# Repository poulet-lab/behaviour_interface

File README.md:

# Behavior Interface

Interface between a data acquisition device on one end as well as, both,
1) input from capacitive lick sensors, and
2) reward output to valves on the other end.

Digital events (licks, rewards) are displayed by means of LEDs.
Circuit breakers can be used to reset the capacitive sensors.

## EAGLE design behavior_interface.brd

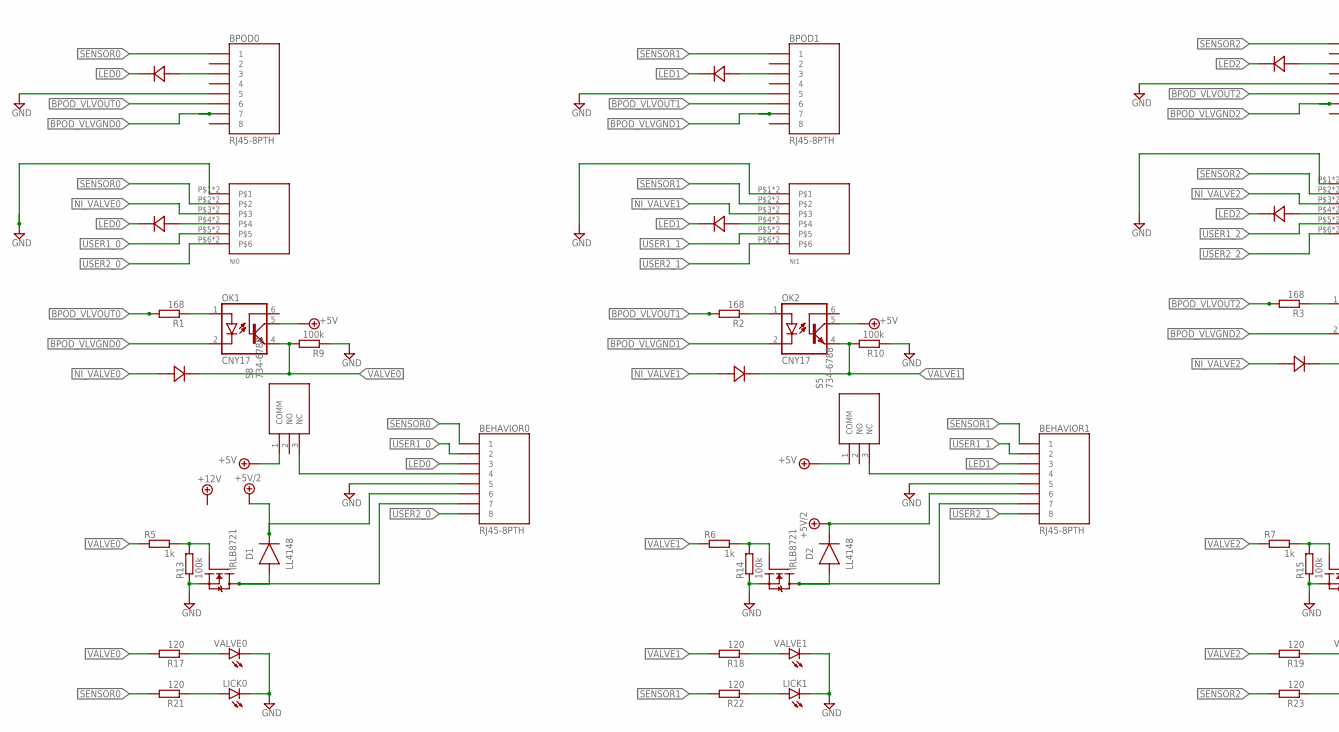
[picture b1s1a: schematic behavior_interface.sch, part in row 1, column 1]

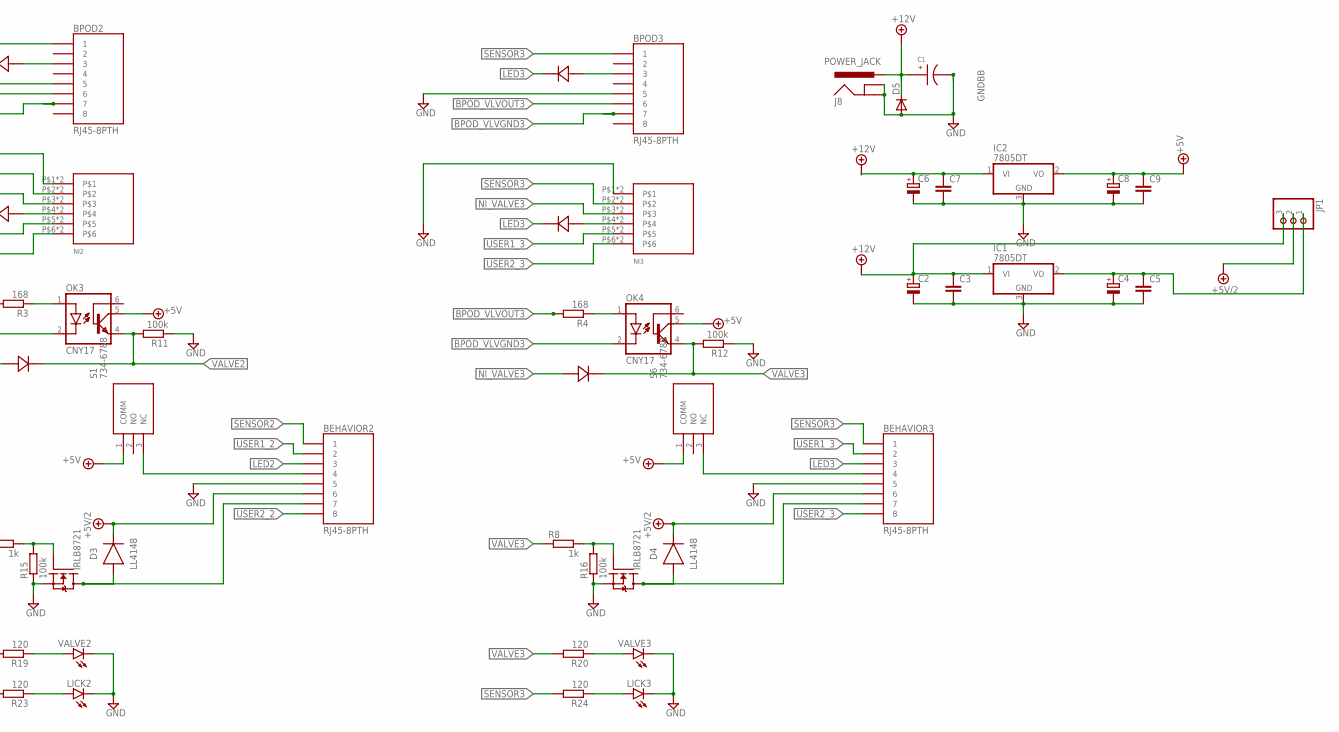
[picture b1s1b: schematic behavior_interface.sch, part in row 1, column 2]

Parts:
BEHAVIOR0, BEHAVIOR1, BEHAVIOR2, BEHAVIOR3: RJ45-8PTH; RJ45-8
BPOD0, BPOD1, BPOD2, BPOD3: RJ45-8PTH; RJ45-8
C1: EEE-FK1H100UR
C2, C4, C6, C8: CPOL-EUD; PANASONIC_D
C3, C5, C7, C9: C-EUC1206; C1206
CR1, CR2, CR3, CR4, CR5, CR6, CR7, CR8, CR9, CR10, CR11, CR12: CUS10S30USC_TOS-M; USC_TOS-M
D1, D2, D3, D4: LL4148; DIOMELF3516
D5: DIODE-DO214AA; DO214AA
IC1, IC2: 7805DT; TO252
J8: POWER_JACK; POWER_JACK_PTH
JP1: PINHD-1X3; 1X03
LICK0, LICK1, LICK2, LICK3: LEDSIDELED; OSRAM-SIDELED
NI0, NI1, NI2, NI3: 1-2834015-6
OK1, OK2, OK3, OK4: CNY17; DIL06
R1, R2, R3, R4: 168; M1206
R5, R6, R7, R8: 1k; M1206
R9, R10, R11, R12, R13, R14, R15, R16: 100k; M1206
R17, R18, R19, R20, R21, R22, R23, R24: 120; M1206
S1, S5, S6, S8: 734-6788; 7346788
SETUP1, SETUP2, SETUP3, SETUP4: IRLB8721; TO220V
VALVE0, VALVE1, VALVE2, VALVE3: LEDSIDELED; OSRAM-SIDELED

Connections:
+5V: C8.+, C9.1, IC2.2 (VO), OK1.5 (COL), OK2.5 (COL), OK3.5 (COL), OK4.5 (COL), S1.1 (COMM), S5.1 (COMM), S6.1 (COMM), S8.1 (COMM)
+5V/2: BEHAVIOR0.6, BEHAVIOR1.6, BEHAVIOR2.6, BEHAVIOR3.6, D1.1 (C), D2.1 (C), D3.1 (C), D4.1 (C), JP1.2
+12V: C1.ANODE, C2.+, C3.1, C6.+, C7.1, D5.C, IC1.1 (VI), IC2.1 (VI), J8.PWR, JP1.3
BPOD_VLVGND0: BPOD0.7, OK1.2 (C)
BPOD_VLVGND1: BPOD1.7, OK2.2 (C)
BPOD_VLVGND2: BPOD2.7, OK3.2 (C)
BPOD_VLVGND3: BPOD3.7, OK4.2 (C)
BPOD_VLVOUT0: BPOD0.6, R1.2
BPOD_VLVOUT1: BPOD1.6, R2.2
BPOD_VLVOUT2: BPOD2.6, R3.2
BPOD_VLVOUT3: BPOD3.6, R4.2
GND: BEHAVIOR0.5, BEHAVIOR1.5, BEHAVIOR2.5, BEHAVIOR3.5, BPOD0.5, BPOD1.5, BPOD2.5, BPOD3.5, C1.CATHODE, C2.-, C3.2, C4.-, C5.2, C6.-, C7.2, C8.-, C9.2, D5.A, IC1.3 (GND), IC2.3 (GND), J8.GND, J8.GNDBREAK, LICK0.C, LICK1.C, LICK2.C, LICK3.C, NI0.P$1, NI0.P$7, NI1.P$1, NI1.P$7, NI2.P$1, NI2.P$7, NI3.P$1, NI3.P$7, R9.1, R10.1, R11.1, R12.1, R13.1, R14.1, R15.1, R16.1, SETUP1.3 (S), SETUP2.3 (S), SETUP3.3 (S), SETUP4.3 (S), VALVE0.C, VALVE1.C, VALVE2.C, VALVE3.C
LED0: BEHAVIOR0.3, CR1.1 (CATHODE), CR5.1 (CATHODE)
LED1: BEHAVIOR1.3, CR2.1 (CATHODE), CR6.1 (CATHODE)
LED2: BEHAVIOR2.3, CR3.1 (CATHODE), CR7.1 (CATHODE)
LED3: BEHAVIOR3.3, CR4.1 (CATHODE), CR8.1 (CATHODE)
unnamed: R5.2, R13.2, SETUP1.1 (G)
unnamed: CR5.2 (ANODE), NI0.P$4, NI0.P$10
unnamed: CR8.2 (ANODE), NI3.P$4, NI3.P$10
unnamed: BEHAVIOR0.7, D1.2 (A), SETUP1.2 (D)
unnamed: BEHAVIOR0.4, S8.3 (NC)
unnamed: OK1.1 (A), R1.1
unnamed: BPOD0.3, CR1.2 (ANODE)
unnamed: CR6.2 (ANODE), NI1.P$4, NI1.P$10
unnamed: LICK0.A, R21.1
unnamed: R17.1, VALVE0.A
unnamed: R6.2, R14.2, SETUP2.1 (G)
unnamed: BEHAVIOR1.7, D2.2 (A), SETUP2.2 (D)
unnamed: BEHAVIOR1.4, S5.3 (NC)
unnamed: OK2.1 (A), R2.1
unnamed: BPOD1.3, CR2.2 (ANODE)
unnamed: CR7.2 (ANODE), NI2.P$4, NI2.P$10
unnamed: LICK1.A, R22.1
unnamed: R18.1, VALVE1.A
unnamed: R7.2, R15.2, SETUP3.1 (G)
unnamed: BEHAVIOR2.7, D3.2 (A), SETUP3.2 (D)
unnamed: BEHAVIOR2.4, S1.3 (NC)
unnamed: OK3.1 (A), R3.1
unnamed: BPOD2.3, CR3.2 (ANODE)
unnamed: LICK2.A, R23.1
unnamed: R19.1, VALVE2.A
unnamed: C4.+, C5.1, IC1.2 (VO), JP1.1
unnamed: R8.2, R16.2, SETUP4.1 (G)
unnamed: BEHAVIOR3.7, D4.2 (A), SETUP4.2 (D)
unnamed: BEHAVIOR3.4, S6.3 (NC)
unnamed: OK4.1 (A), R4.1
unnamed: BPOD3.3, CR4.2 (ANODE)
unnamed: LICK3.A, R24.1
unnamed: R20.1, VALVE3.A
NI_VALVE0: CR9.2 (ANODE), NI0.P$3, NI0.P$9
NI_VALVE1: CR10.2 (ANODE), NI1.P$3, NI1.P$9
NI_VALVE2: CR11.2 (ANODE), NI2.P$3, NI2.P$9
NI_VALVE3: CR12.2 (ANODE), NI3.P$3, NI3.P$9
SENSOR0: BEHAVIOR0.1, BPOD0.1, NI0.P$2, NI0.P$8, R21.2
SENSOR1: BEHAVIOR1.1, BPOD1.1, NI1.P$2, NI1.P$8, R22.2
SENSOR2: BEHAVIOR2.1, BPOD2.1, NI2.P$2, NI2.P$8, R23.2
SENSOR3: BEHAVIOR3.1, BPOD3.1, NI3.P$2, NI3.P$8, R24.2
USER1_0: BEHAVIOR0.2, NI0.P$5, NI0.P$11
USER1_1: BEHAVIOR1.2, NI1.P$5, NI1.P$11
USER1_2: BEHAVIOR2.2, NI2.P$5, NI2.P$11
USER1_3: BEHAVIOR3.2, NI3.P$5, NI3.P$11
USER2_0: BEHAVIOR0.8, NI0.P$6, NI0.P$12
USER2_1: BEHAVIOR1.8, NI1.P$6, NI1.P$12
USER2_2: BEHAVIOR2.8, NI2.P$6, NI2.P$12
USER2_3: BEHAVIOR3.8, NI3.P$6, NI3.P$12
VALVE0: CR9.1 (CATHODE), OK1.4 (EMI), R5.1, R9.2, R17.2
VALVE1: CR10.1 (CATHODE), OK2.4 (EMI), R6.1, R10.2, R18.2
VALVE2: CR11.1 (CATHODE), OK3.4 (EMI), R7.1, R11.2, R19.2
VALVE3: CR12.1 (CATHODE), OK4.4 (EMI), R8.1, R12.2, R20.2

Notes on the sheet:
GNDBB

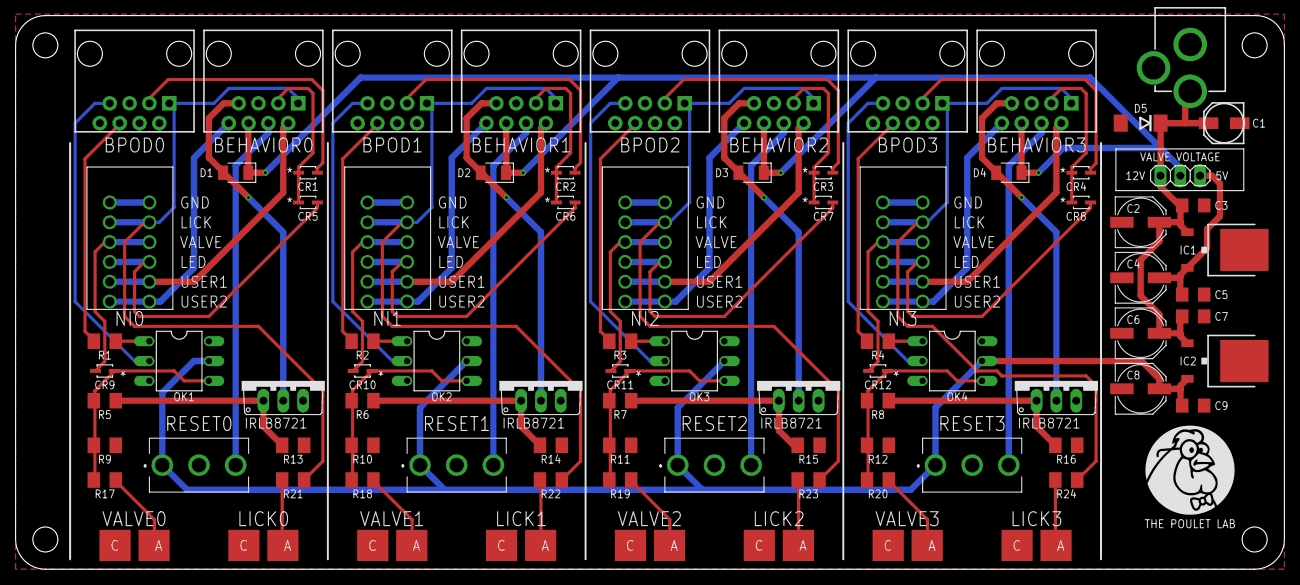
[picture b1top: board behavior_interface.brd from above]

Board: 2 copper layers, 162.6 x 70.9 mm, 86 parts (0 on the bottom side), 69 nets.

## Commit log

2022-05-10 update to latest version
2022-05-10 update enclosure

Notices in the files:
parts and their libraries:
SparkFun-Connectors: Licensing: Creative Commons ShareAlike 4.0 International - https://creativecommons.org/licenses/by-sa/4.0
COPYRIGHT: Copyright (C) 2016 Accelerated Designs. All rights reserved
